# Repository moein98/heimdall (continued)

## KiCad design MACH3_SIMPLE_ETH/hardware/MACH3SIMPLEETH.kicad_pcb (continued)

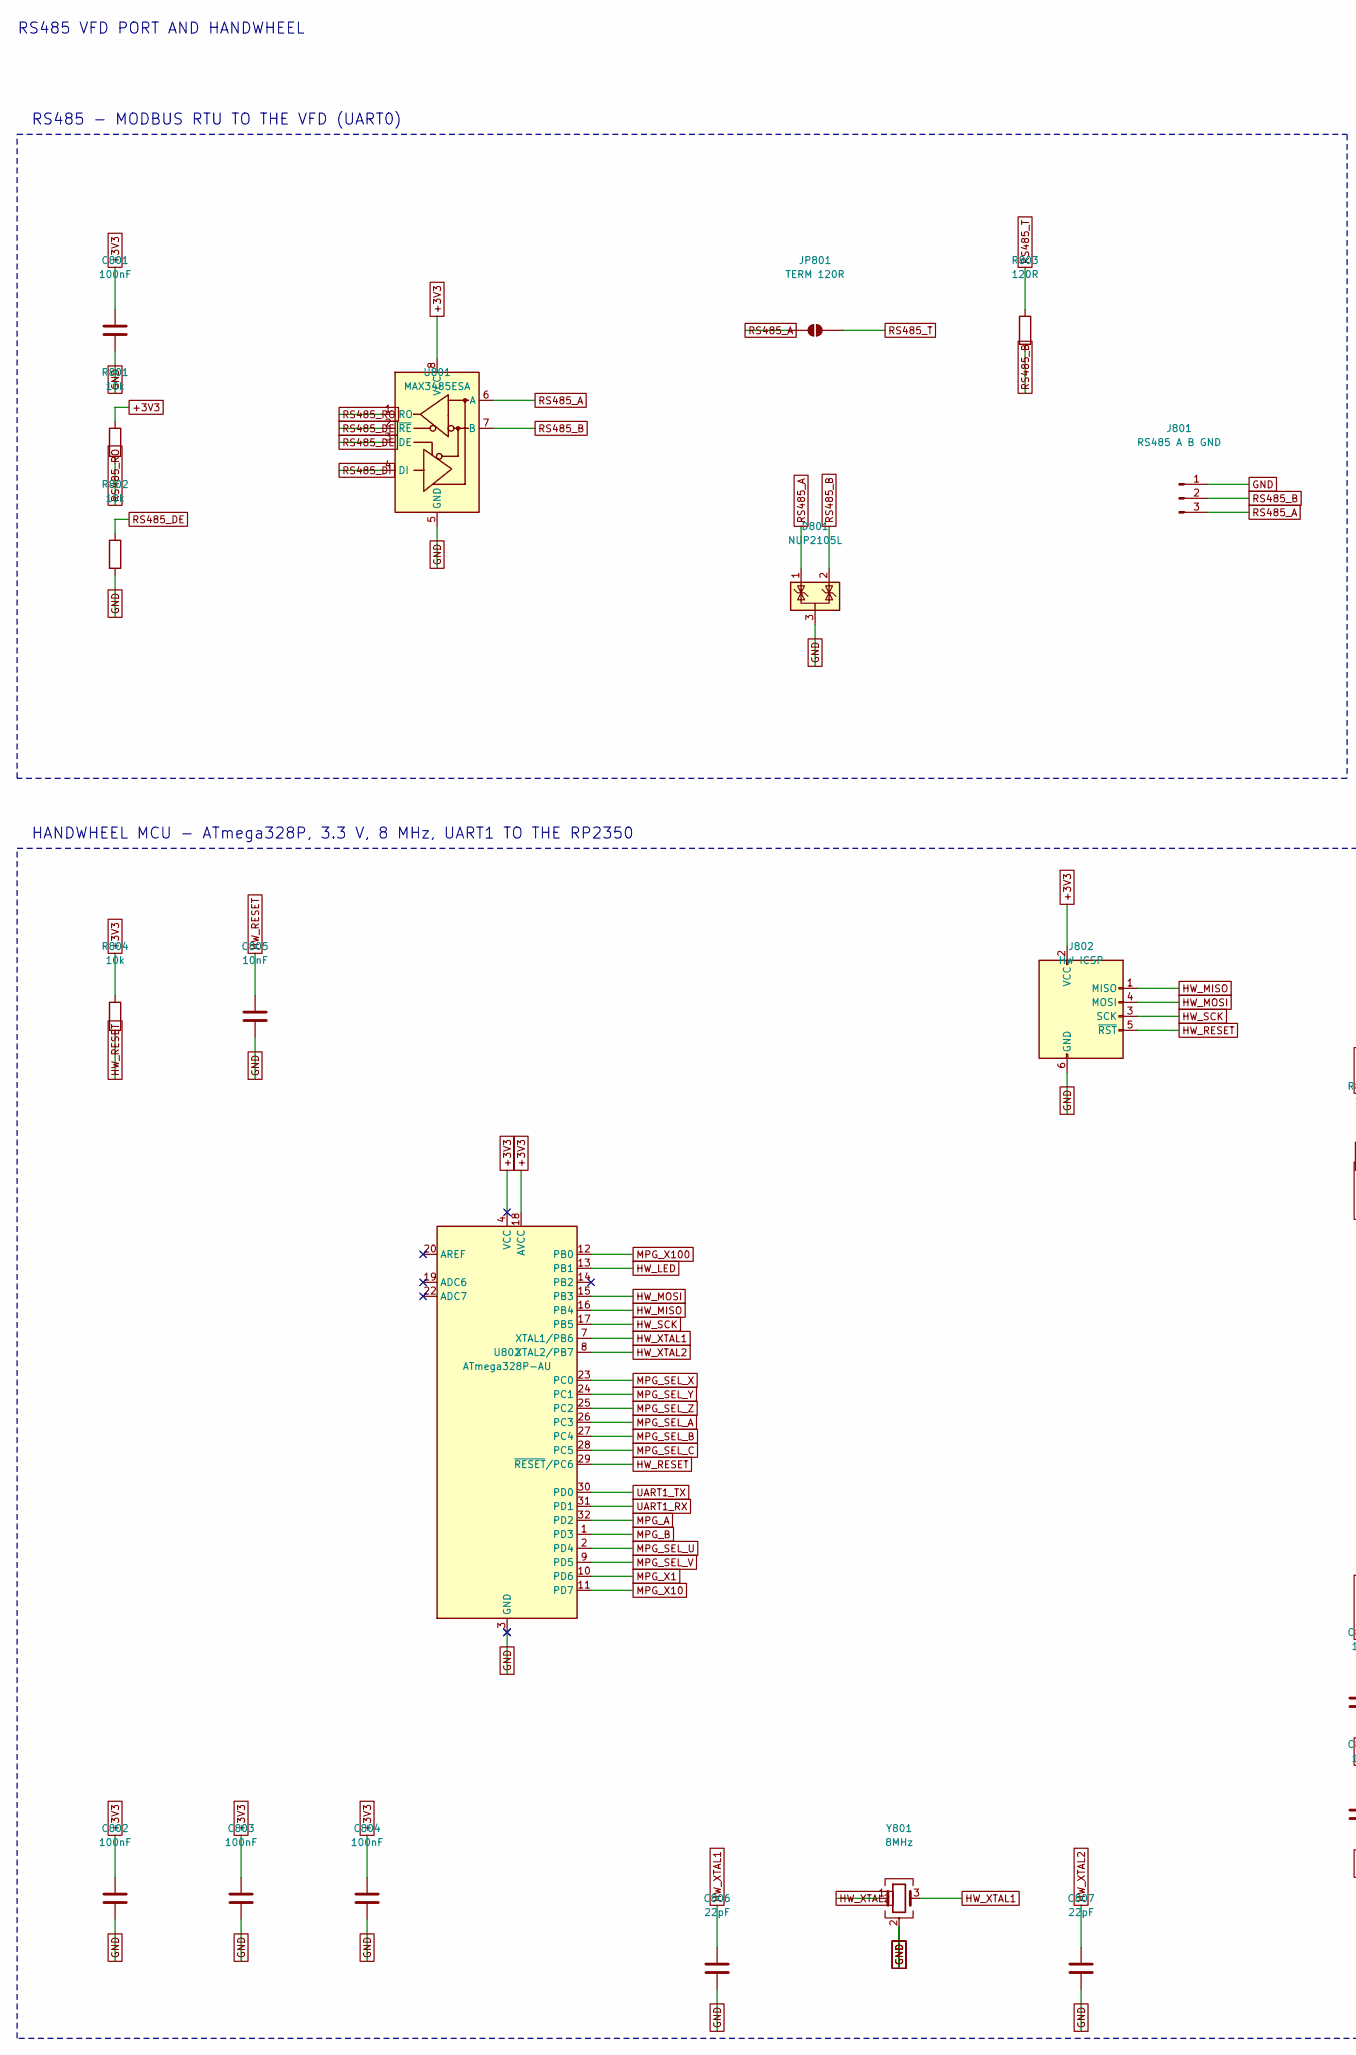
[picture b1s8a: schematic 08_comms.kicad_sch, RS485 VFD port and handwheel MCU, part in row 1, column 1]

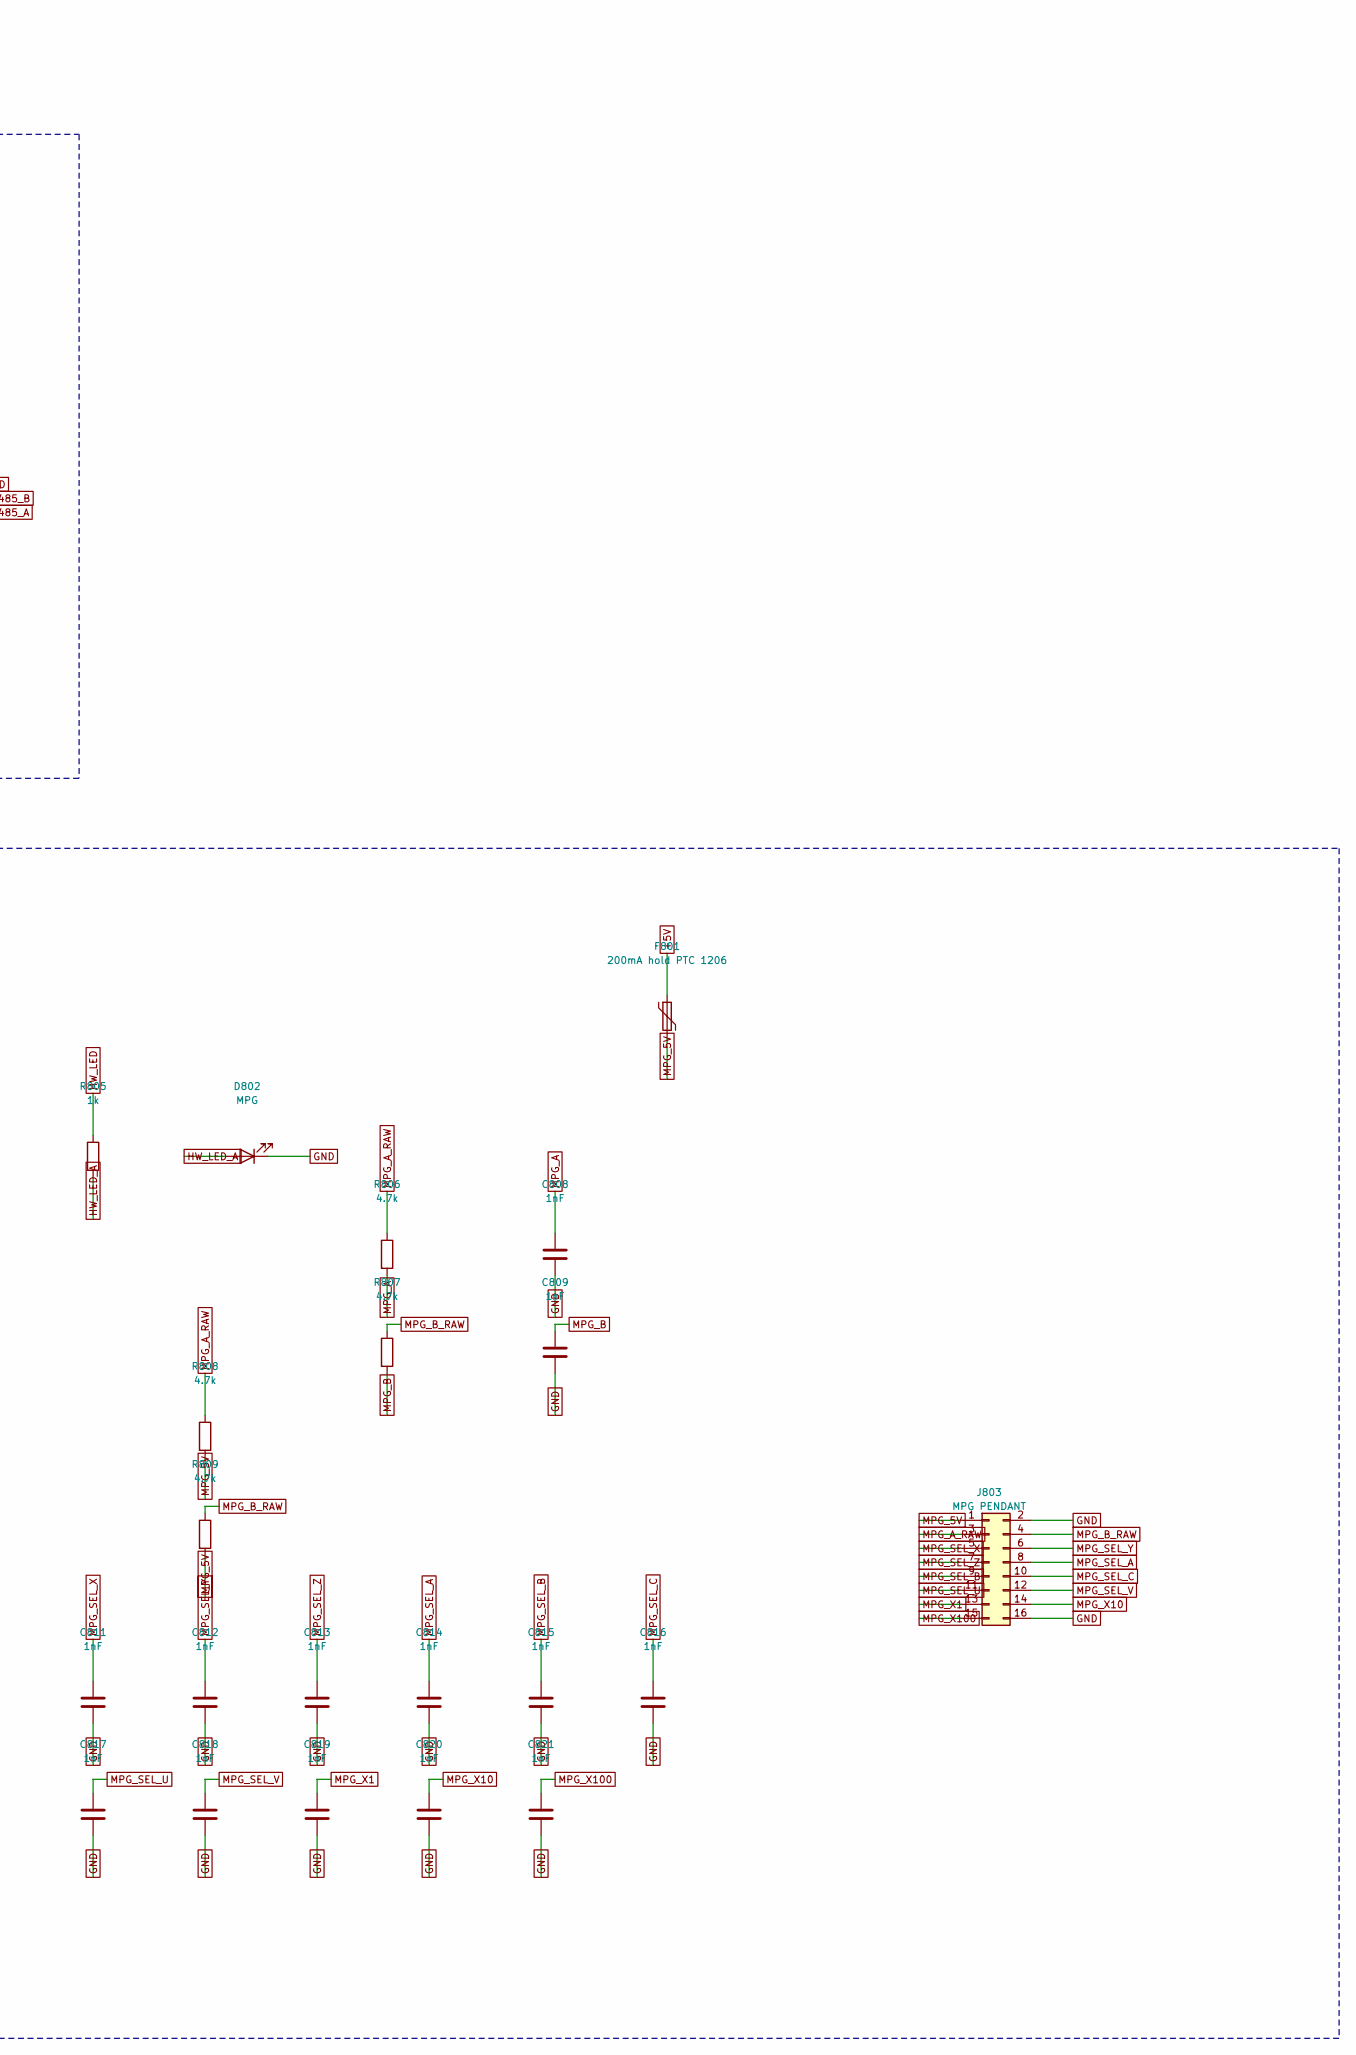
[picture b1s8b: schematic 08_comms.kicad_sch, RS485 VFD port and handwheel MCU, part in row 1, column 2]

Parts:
C801, C802, C803, C804: 100nF; C_0603_1608Metric
C805: 10nF; C_0603_1608Metric
C806, C807: 22pF; C_0603_1608Metric
C808, C809, C811, C812, C813, C814, C815, C816, C817, C818, C819, C820, C821: 1nF; C_0603_1608Metric
D801: NUP2105L; SOT-23
D802: MPG; LED_0603_1608Metric
F801: 200mA hold PTC 1206; Fuse_1206_3216Metric
J801: RS485 A B GND; TerminalBlock_Phoenix_MKDS-1,5-3_1x03_P5.00mm_Horizontal
J802: HW ICSP; PinHeader_2x03_P2.54mm_Vertical
J803: MPG PENDANT; IDC-Header_2x08_P2.54mm_Vertical
JP801: TERM 120R; SolderJumper-2_P1.3mm_Open_RoundedPad1.0x1.5mm
R801, R802, R804: 10k; R_0603_1608Metric
R803: 120R; R_0603_1608Metric
R805: 1k; R_0603_1608Metric
R806, R807, R808, R809: 4.7k; R_0603_1608Metric
U801: MAX3485ESA; SOIC-8_3.9x4.9mm_P1.27mm
U802: ATmega328P-AU; TQFP-32_7x7mm_P0.8mm
Y801: 8MHz; Crystal_SMD_3225-4Pin_3.2x2.5mm

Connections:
+3V3: C801.1, C802.1, C803.1, C804.1, J802.2 (VCC), R801.1, R804.1, U801.8 (VCC), U802.4 (VCC), U802.6 (VCC), U802.18 (AVCC); also elsewhere on the board
+5V: F801.1; also elsewhere on the board
GND: C801.2, C802.2, C803.2, C804.2, C805.2, C806.2, C807.2, C808.2, C809.2, C811.2, C812.2, C813.2, C814.2, C815.2, C816.2, C817.2, C818.2, C819.2, C820.2, C821.2, D801.3 (A), D802.1 (K), J801.1, J802.6 (GND), J803.2, J803.16, R802.2, U801.5 (GND), U802.3 (GND), U802.5 (GND), U802.21 (GND), Y801.2 (G), Y801.4 (G); also elsewhere on the board
HW_LED: R805.1, U802.13 (PB1)
HW_LED_A: D802.2 (A), R805.2
HW_MISO: J802.1 (MISO), U802.16 (PB4)
HW_MOSI: J802.4 (MOSI), U802.15 (PB3)
HW_RESET: C805.1, J802.5 (~RST), R804.2, U802.29 (~RESET/PC6)
HW_SCK: J802.3 (SCK), U802.17 (PB5)
HW_XTAL1: C806.1, U802.7 (XTAL1/PB6), Y801.3
HW_XTAL2: C807.1, U802.8 (XTAL2/PB7), Y801.1
MPG_5V: F801.2, J803.1, R808.2, R809.2
MPG_A: C808.1, R806.2, U802.32 (PD2)
MPG_A_RAW: J803.3, R806.1, R808.1
MPG_B: C809.1, R807.2, U802.1 (PD3)
MPG_B_RAW: J803.4, R807.1, R809.1
MPG_SEL_A: C814.1, J803.8, U802.26 (PC3)
MPG_SEL_B: C815.1, J803.9, U802.27 (PC4)
MPG_SEL_C: C816.1, J803.10, U802.28 (PC5)
MPG_SEL_U: C817.1, J803.11, U802.2 (PD4)
MPG_SEL_V: C818.1, J803.12, U802.9 (PD5)
MPG_SEL_X: C811.1, J803.5, U802.23 (PC0)
MPG_SEL_Y: C812.1, J803.6, U802.24 (PC1)
MPG_SEL_Z: C813.1, J803.7, U802.25 (PC2)
MPG_X1: C819.1, J803.13, U802.10 (PD6)
MPG_X10: C820.1, J803.14, U802.11 (PD7)
MPG_X100: C821.1, J803.15, U802.12 (PB0)
RS485_A: D801.1 (K), J801.3, JP801.1 (A), U801.6 (A)
RS485_B: D801.2 (K), J801.2, R803.2, U801.7 (B)
RS485_DE: R802.1, U801.2 (~RE), U801.3 (DE); also elsewhere on the board
RS485_DI: U801.4 (DI); also elsewhere on the board
RS485_RO: R801.2, U801.1 (RO); also elsewhere on the board
RS485_T: JP801.2 (B), R803.1
UART1_RX: U802.31 (PD1); also elsewhere on the board
UART1_TX: U802.30 (PD0); also elsewhere on the board

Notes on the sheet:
RS485 VFD PORT AND HANDWHEEL
RS485 - MODBUS RTU TO THE VFD (UART0)
HANDWHEEL MCU - ATmega328P, 3.3 V, 8 MHz, UART1 TO THE RP2350

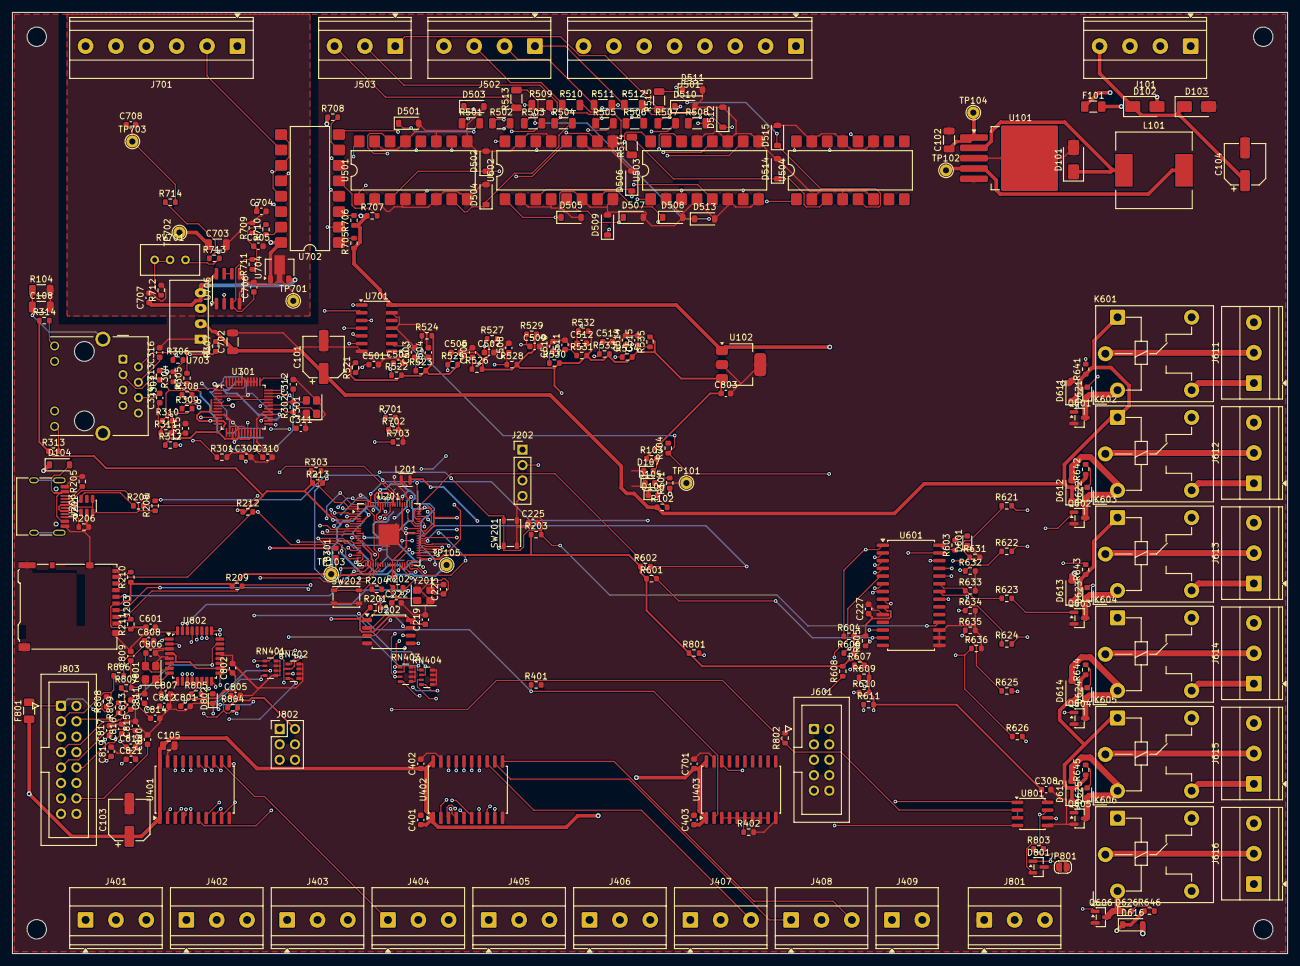
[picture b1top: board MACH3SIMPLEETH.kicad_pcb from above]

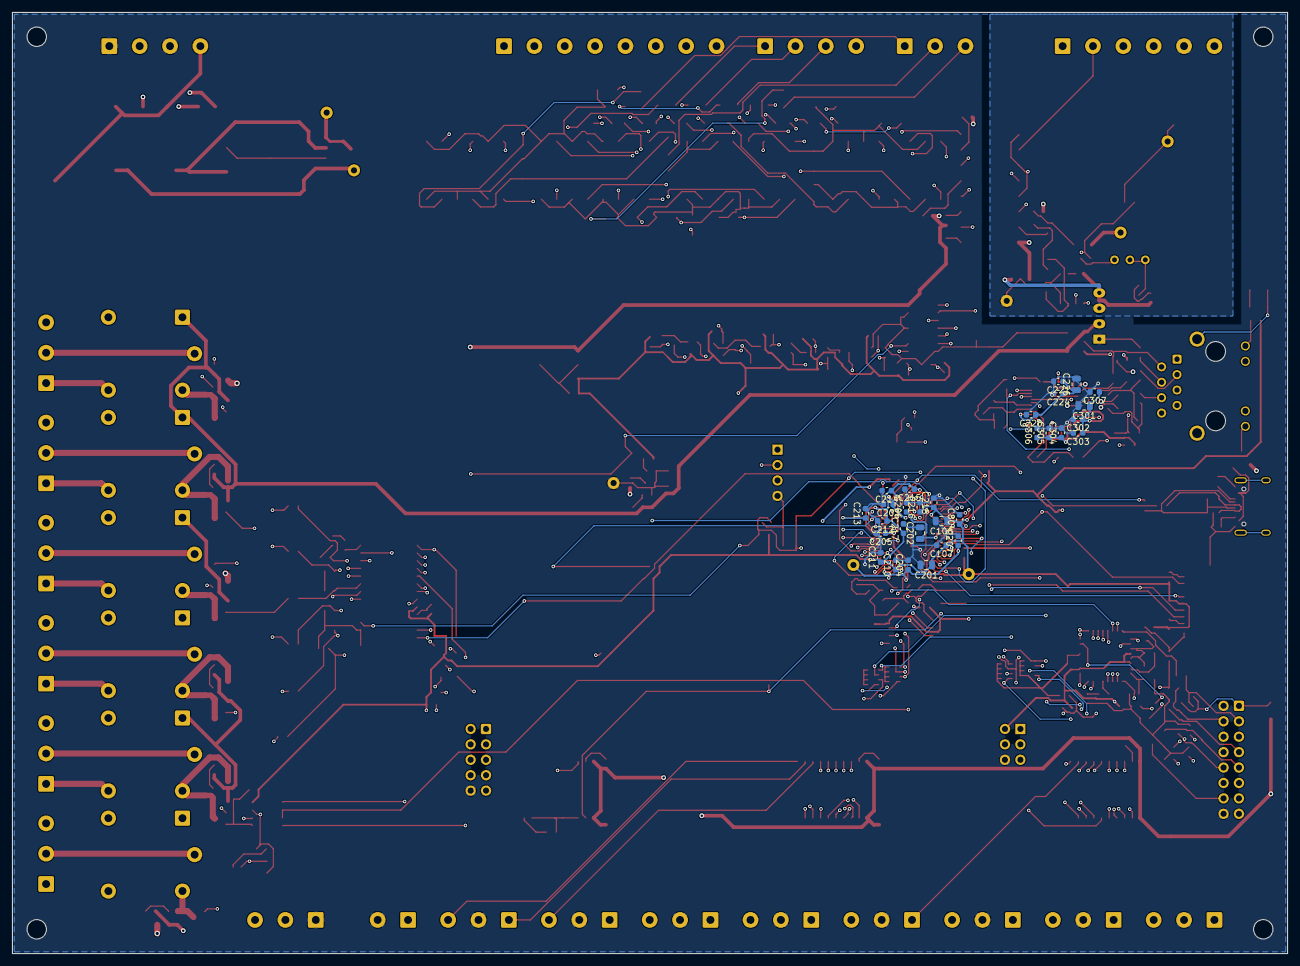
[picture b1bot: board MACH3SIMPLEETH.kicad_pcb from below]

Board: 4 copper layers, 210.0 x 155.0 mm, 337 parts (30 on the bottom side), 257 nets.

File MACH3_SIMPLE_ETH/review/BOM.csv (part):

"Reference","Value","Footprint"
"C101","47uF 50V","Capacitor_SMD:CP_Elec_6.3x7.7"
"C102","1uF 50V X7R","Capacitor_SMD:C_1206_3216Metric"
"C103","220uF 16V low ESR","Capacitor_SMD:CP_Elec_6.3x7.7"
"C104","47uF 50V","Capacitor_SMD:CP_Elec_6.3x7.7"
"C105","10uF 16V X7R","Capacitor_SMD:C_0805_2012Metric"
"C106","10uF 16V X7R","Capacitor_SMD:C_0805_2012Metric"
"C107","100nF","Capacitor_SMD:C_0603_1608Metric"
"C108","1nF 2kV X7R 1206","Capacitor_SMD:C_1206_3216Metric"
"C201","10uF 0805 X5R","Capacitor_SMD:C_0805_2012Metric"
"C202","10uF 0805 X5R","Capacitor_SMD:C_0805_2012Metric"
"C203","2.2uF","Capacitor_SMD:C_0603_1608Metric"
"C204","100nF","Capacitor_SMD:C_0603_1608Metric"
"C205","100nF","Capacitor_SMD:C_0603_1608Metric"
"C206","100nF","Capacitor_SMD:C_0603_1608Metric"
"C207","1uF","Capacitor_SMD:C_0603_1608Metric"
"C210","100nF","Capacitor_SMD:C_0603_1608Metric"
"C211","100nF","Capacitor_SMD:C_0603_1608Metric"
"C212","100nF","Capacitor_SMD:C_0603_1608Metric"
"C213","100nF","Capacitor_SMD:C_0603_1608Metric"
"C214","100nF","Capacitor_SMD:C_0603_1608Metric"
"C215","100nF","Capacitor_SMD:C_0603_1608Metric"
"C216","100nF","Capacitor_SMD:C_0603_1608Metric"
"C217","100nF","Capacitor_SMD:C_0603_1608Metric"
"C218","100nF","Capacitor_SMD:C_0603_1608Metric"
"C219","100nF","Capacitor_SMD:C_0603_1608Metric"
"C220","100nF","Capacitor_SMD:C_0603_1608Metric"
"C221","4.7uF","Capacitor_SMD:C_0603_1608Metric"
"C222","15pF","Capacitor_SMD:C_0603_1608Metric"
"C223","15pF","Capacitor_SMD:C_0603_1608Metric"
"C224","100nF","Capacitor_SMD:C_0603_1608Metric"
"C225","1uF","Capacitor_SMD:C_0603_1608Metric"
"C226","10uF 0805","Capacitor_SMD:C_0805_2012Metric"
"C227","100nF","Capacitor_SMD:C_0603_1608Metric"
"C301","10uF 0805","Capacitor_SMD:C_0805_2012Metric"
"C302","100nF","Capacitor_SMD:C_0603_1608Metric"
"C303","100nF","Capacitor_SMD:C_0603_1608Metric"
"C304","100nF","Capacitor_SMD:C_0603_1608Metric"
"C305","100nF","Capacitor_SMD:C_0603_1608Metric"
"C306","100nF","Capacitor_SMD:C_0603_1608Metric"
"C307","100nF","Capacitor_SMD:C_0603_1608Metric"
"C308","100nF","Capacitor_SMD:C_0603_1608Metric"
"C309","4.7uF","Capacitor_SMD:C_0603_1608Metric"
"C310","100nF","Capacitor_SMD:C_0603_1608Metric"
"C311","18pF","Capacitor_SMD:C_0603_1608Metric"
"C312","18pF","Capacitor_SMD:C_0603_1608Metric"
"C313","6.8nF","Capacitor_SMD:C_0603_1608Metric"
"C314","6.8nF","Capacitor_SMD:C_0603_1608Metric"
"C315","100nF","Capacitor_SMD:C_0603_1608Metric"
"C316","22nF","Capacitor_SMD:C_0603_1608Metric"
"C401","100nF","Capacitor_SMD:C_0603_1608Metric"
"C402","100nF","Capacitor_SMD:C_0603_1608Metric"
"C403","100nF","Capacitor_SMD:C_0603_1608Metric"
"C501","10nF","Capacitor_SMD:C_0603_1608Metric"
"C502","10nF","Capacitor_SMD:C_0603_1608Metric"
"C503","10nF","Capacitor_SMD:C_0603_1608Metric"
"C504","10nF","Capacitor_SMD:C_0603_1608Metric"
"C505","10nF","Capacitor_SMD:C_0603_1608Metric"
"C506","10nF","Capacitor_SMD:C_0603_1608Metric"
"C507","10nF","Capacitor_SMD:C_0603_1608Metric"
"C508","10nF","Capacitor_SMD:C_0603_1608Metric"
"C509","10nF","Capacitor_SMD:C_0603_1608Metric"
"C510","10nF","Capacitor_SMD:C_0603_1608Metric"
"C511","10nF","Capacitor_SMD:C_0603_1608Metric"
"C512","10nF","Capacitor_SMD:C_0603_1608Metric"
"C513","10nF","Capacitor_SMD:C_0603_1608Metric"
"C514","10nF","Capacitor_SMD:C_0603_1608Metric"
"C515","10nF","Capacitor_SMD:C_0603_1608Metric"
"C601","100nF","Capacitor_SMD:C_0603_1608Metric"
"C701","100nF","Capacitor_SMD:C_0603_1608Metric"
"C702","1uF 50V X7R","Capacitor_SMD:C_1206_3216Metric"
"C703","10uF 25V X7R","Capacitor_SMD:C_1206_3216Metric"
"C704","1uF","Capacitor_SMD:C_0603_1608Metric"
"C705","470nF","Capacitor_SMD:C_0603_1608Metric"
"C706","470nF","Capacitor_SMD:C_0603_1608Metric"
"C707","100nF","Capacitor_SMD:C_0603_1608Metric"
"C708","10nF","Capacitor_SMD:C_0603_1608Metric"
"C801","100nF","Capacitor_SMD:C_0603_1608Metric"
"C802","100nF","Capacitor_SMD:C_0603_1608Metric"
"C803","100nF","Capacitor_SMD:C_0603_1608Metric"
"C804","100nF","Capacitor_SMD:C_0603_1608Metric"
"C805","10nF","Capacitor_SMD:C_0603_1608Metric"
"C806","22pF","Capacitor_SMD:C_0603_1608Metric"
"C807","22pF","Capacitor_SMD:C_0603_1608Metric"
"C808","1nF","Capacitor_SMD:C_0603_1608Metric"
"C809","1nF","Capacitor_SMD:C_0603_1608Metric"
"C811","1nF","Capacitor_SMD:C_0603_1608Metric"
"C812","1nF","Capacitor_SMD:C_0603_1608Metric"
"C813","1nF","Capacitor_SMD:C_0603_1608Metric"
"C814","1nF","Capacitor_SMD:C_0603_1608Metric"
"C815","1nF","Capacitor_SMD:C_0603_1608Metric"
"C816","1nF","Capacitor_SMD:C_0603_1608Metric"
"C817","1nF","Capacitor_SMD:C_0603_1608Metric"
"C818","1nF","Capacitor_SMD:C_0603_1608Metric"
"C819","1nF","Capacitor_SMD:C_0603_1608Metric"
"C820","1nF","Capacitor_SMD:C_0603_1608Metric"
"C821","1nF","Capacitor_SMD:C_0603_1608Metric"
"D101","SS34 catch","Diode_SMD:D_SMA"
"D102","SS34 reverse","Diode_SMD:D_SMA"
"D103","SMAJ26A","Diode_SMD:D_SMA"
"D104","B5819W","Diode_SMD:D_SOD-123"
"D105","+5V","LED_SMD:LED_0603_1608Metric"
"D106","V24","LED_SMD:LED_0603_1608Metric"
"D107","+3V3","LED_SMD:LED_0603_1608Metric"
"D501","1N4148W","Diode_SMD:D_SOD-123"
"D502","1N4148W","Diode_SMD:D_SOD-123"
"D503","1N4148W","Diode_SMD:D_SOD-123"
"D504","1N4148W","Diode_SMD:D_SOD-123"
"D505","1N4148W","Diode_SMD:D_SOD-123"
"D506","1N4148W","Diode_SMD:D_SOD-123"
"D507","1N4148W","Diode_SMD:D_SOD-123"
"D508","1N4148W","Diode_SMD:D_SOD-123"
"D509","1N4148W","Diode_SMD:D_SOD-123"
"D510","1N4148W","Diode_SMD:D_SOD-123"
"D511","1N4148W","Diode_SMD:D_SOD-123"
"D512","1N4148W","Diode_SMD:D_SOD-123"
"D513","1N4148W","Diode_SMD:D_SOD-123"
"D514","1N4148W","Diode_SMD:D_SOD-123"
"D515","1N4148W","Diode_SMD:D_SOD-123"
"D601","STATUS","LED_SMD:LED_0603_1608Metric"
"D611","1N4148W flyback","Diode_SMD:D_SOD-123"
"D612","1N4148W flyback","Diode_SMD:D_SOD-123"
"D613","1N4148W flyback","Diode_SMD:D_SOD-123"
"D614","1N4148W flyback","Diode_SMD:D_SOD-123"
"D615","1N4148W flyback","Diode_SMD:D_SOD-123"
"D616","1N4148W flyback","Diode_SMD:D_SOD-123"
"D621","KA","LED_SMD:LED_0603_1608Metric"
"D622","KB","LED_SMD:LED_0603_1608Metric"
"D623","KC","LED_SMD:LED_0603_1608Metric"
"D624","KD","LED_SMD:LED_0603_1608Metric"
"D625","KE","LED_SMD:LED_0603_1608Metric"
"D626","KF","LED_SMD:LED_0603_1608Metric"
"D801","NUP2105L","Package_TO_SOT_SMD:SOT-23"
"D802","MPG","LED_SMD:LED_0603_1608Metric"
"F101","1A slow 1206","Fuse:Fuse_1206_3216Metric"
"F801","200mA hold PTC 1206","Fuse:Fuse_1206_3216Metric"
"FB301","120R@100MHz 0603","Inductor_SMD:L_0603_1608Metric"
"J101","SENSORS / 24V IN","TerminalBlock_Phoenix:TerminalBlock_Phoenix_MKDS-1,5-4_1x04_P5.00mm_Horizontal"
"J201","USB-C","Connector_USB:USB_C_Receptacle_HRO_TYPE-C-31-M-12"
"J202","SWD","Connector_PinHeader_2.54mm:PinHeader_1x04_P2.54mm_Vertical"
"J203","microSD","Connector_Card:microSD_HC_Hirose_DM3AT-SF-PEJM5"
"J301","HR911105A","Connector_RJ:RJ45_Hanrun_HR911105A_Horizontal"
"J401","X axis","TerminalBlock_Phoenix:TerminalBlock_Phoenix_MKDS-1,5-3_1x03_P5.00mm_Horizontal"
"J402","Y axis","TerminalBlock_Phoenix:TerminalBlock_Phoenix_MKDS-1,5-3_1x03_P5.00mm_Horizontal"
"J403","Z axis","TerminalBlock_Phoenix:TerminalBlock_Phoenix_MKDS-1,5-3_1x03_P5.00mm_Horizontal"
"J404","A axis","TerminalBlock_Phoenix:TerminalBlock_Phoenix_MKDS-1,5-3_1x03_P5.00mm_Horizontal"
"J405","B axis","TerminalBlock_Phoenix:TerminalBlock_Phoenix_MKDS-1,5-3_1x03_P5.00mm_Horizontal"
"J406","C axis","TerminalBlock_Phoenix:TerminalBlock_Phoenix_MKDS-1,5-3_1x03_P5.00mm_Horizontal"
"J407","U axis","TerminalBlock_Phoenix:TerminalBlock_Phoenix_MKDS-1,5-3_1x03_P5.00mm_Horizontal"
"J408","V axis","TerminalBlock_Phoenix:TerminalBlock_Phoenix_MKDS-1,5-3_1x03_P5.00mm_Horizontal"
"J409","ENABLE","TerminalBlock_Phoenix:TerminalBlock_Phoenix_MKDS-1,5-2_1x02_P5.00mm_Horizontal"
"J501","LIMITS X Y Z A B C U V","TerminalBlock_Phoenix:TerminalBlock_Phoenix_MKDS-1,5-8_1x08_P5.00mm_Horizontal"
"J502","EST HLD RUN PRB","TerminalBlock_Phoenix:TerminalBlock_Phoenix_MKDS-1,5-4_1x04_P5.00mm_Horizontal"
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
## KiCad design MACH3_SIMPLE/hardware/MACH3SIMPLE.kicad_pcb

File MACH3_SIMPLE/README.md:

# MACH3-SIMPLE (revision A1)

A Mach3 parallel-port breakout board: six buffered step/dir axes, six 24 V
sensor inputs, a handwheel switched between jog and THC, six relays driven
over RS232 by an ATmega328P, and an isolated 0-10 V spindle-speed output with
FWD / REV for a VFD. It reproduces a board already in service and matches its
connector positions. It takes one supply, 24 V; the 5 V rail is made on the
board. Apart from the VFD port there is no galvanic isolation.

| Folder | What is in it |
|---|---|
| `fab/` | **What goes to the board house.** `MACH3SIMPLE-gerbers.zip` (2 layers, 1.6 mm FR4, 1 oz, 150.5 x 137.9 mm), BOM, pick-and-place, PDFs |
| `hardware/` | The KiCad 10 project: `MACH3SIMPLE.kicad_pro` |
| `firmware/` | AVR C source; `build/mach3simple.hex` is the built firmware |
| `docs/` | `SPEC.md` - what the board is and why; `COMMISSIONING.md` - bring-up and test, step by step (Persian) |
| `tools/` | The scripts that generate, check and route the design |
| `review/` | ERC/DRC reports, netlist, schematic PDF, board renders |

## What changed from A0

| | A0 | A1 |
|---|---|---|
| Supplies | 5 V and 24 V, each on its own terminal | **24 V only.** An LM2596S-5.0 buck (`U4`) makes +5V, in the top-right corner beside the 24 V input |
| Relay drivers | 2N7002 drain and source swapped - every relay **stuck on** | Fixed. `check_design.py` now checks every MOSFET's source is on ground |
| Top-edge terminal legends | Printed in reverse: `+24` over 0V, `+5` over the handwheel's B, `EMG` over X home | Fixed: the signals follow the legends, which follow the board in service |
| Input optocouplers | PC847 on a SOIC-16 footprint, which no PC847 fits | SMD DIP-16 (2.54 mm), the package PC847 comes in |
| Opto LED protection | Promised in the notes, missing from the circuit | A reverse diode across every input LED (`D20`-`D25`) |
| Spindle | - | **New:** isolated 0-10 V (`AVI`/`ACM`) and FWD/REV/AUX (`FWD`/`REV`/`AUX`/`DCM`) on `J5`, from port 2 pins 7, 8, 9, 6 |

A1 then had a design review of its own, which added:

| | |
|---|---|
| Relay terminals | legends printed on the back (`RELAY A`, `NO COM NC` under each screw) and `RELAY A`-`F` on the front; A0/A1 had them on F.Fab only, which is not printed |
| Relay LED resistors | 10k instead of 4k7 - 4k7 on 24 V was 103 mW in a 100 mW 0603 |
| Axis buffers | 74AC245 (same pads): 24 mA per output for opto-input drivers |
| Sensor supply | `J4` is four screws: `+24 0V` for the sensors (fused) and `+24 0V` in |
| C2 | 47 uF 50 V - a 100 uF 50 V part does not come in a 6.3 x 7.7 can |
| Labels | `5V`, `24V`, `SERIAL`, relay letters, `10V ADJ` instead of bare designators; a dashed line round the isolated VFD side |
| Test points | `GND` `5V` `24V`, and on the VFD side `ACM` `12V` `AVI` |
| Buck switch node | drawn by hand on the top layer, 14 mm and no vias (was 17 mm with two) |
| Handwheel +5 V | through a 200 mA resettable fuse (`F3`) |
| MCU reset | 10 nF against relay noise |
| VFD `AUX` | the spare optocoupler channel as a fourth VFD contact, port 2 pin 6 |

## Regenerating

The schematic and board are generated by scripts, not drawn by hand. To change
the design, edit `tools/build_project.py` or `tools/build_pcb.py` and
regenerate; an edit made in KiCad is lost at the next regeneration.

    python tools/build_project.py                  # schematic
    D:/KiCad/bin/python.exe tools/build_pcb.py --force   # placement (discards routing)
    D:/KiCad/bin/python.exe tools/autoroute.py export    # then Freerouting, then:
    D:/KiCad/bin/python.exe tools/autoroute.py import
    D:/KiCad/bin/python.exe tools/autoroute.py vfd-export  # then Freerouting on the _vfd DSN
    D:/KiCad/bin/python.exe tools/autoroute.py vfd-import
    D:/KiCad/bin/python.exe tools/autoroute.py stitch
    KICAD_CLI=D:/KiCad/bin/kicad-cli.exe sh tools/validate.sh
    KICAD_CLI=D:/KiCad/bin/kicad-cli.exe sh tools/fab.sh

`build_pcb.py` needs the netlist that `validate.sh` exports (`review/net.net`),
so after a schematic change run `validate.sh` once before placing. It prints
which signal lands under each word of every top-edge legend - read those lines.

## Firmware

`sh firmware/build.sh` runs the tests and builds the hex;
`sh firmware/build.sh flash` also sets the fuses and programs the chip through
the ICSP header `J60` with a USBasp. Serial is 9600 8N1. Commands, sent with
Mach3's `SendSerial`: `A`-`F` relay on, `a`-`f` off, `T` handwheel to THC,
`t` handwheel to jog, `?` status. A1 needs no firmware change.

## Spindle, in Mach3

Port 2 pin 7 is the spindle PWM pin (PWMBase Freq 100 Hz), pin 8 is Output #1
(M3, FWD) and pin 9 Output #2 (M4, REV), all active high. Trim `RV1` for
10.0 V at full PWM. Pin 6 can be Output #3, for `AUX`. `docs/COMMISSIONING.md`,
steps 6 to 8, has the settings.

`mach3 rs232 inputs 6 outputs 6 - pulse 5v - pnp sens.pdf` is the assembly
drawing of the board in service that the layout was copied from.

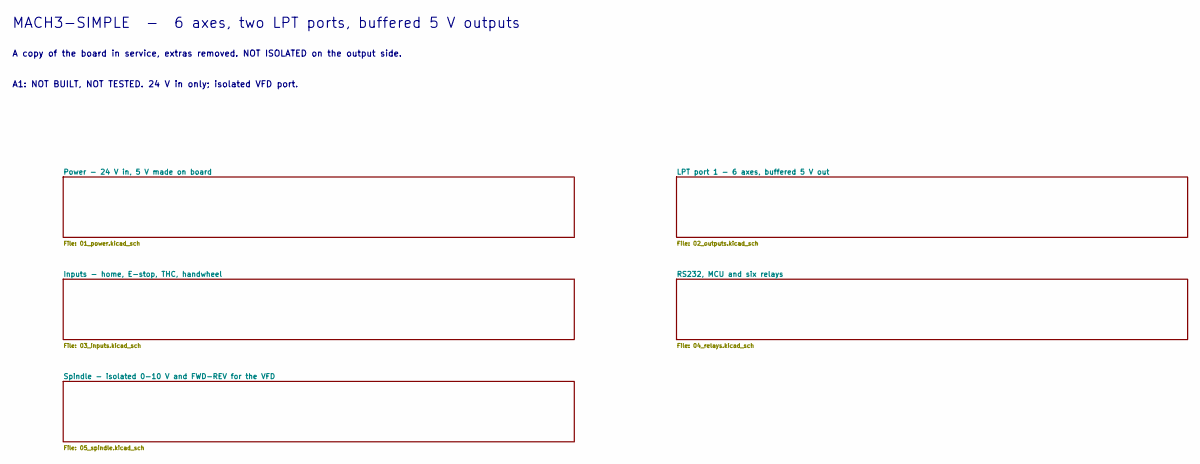
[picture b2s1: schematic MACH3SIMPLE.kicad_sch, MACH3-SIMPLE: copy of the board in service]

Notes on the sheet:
MACH3-SIMPLE - 6 axes, two LPT ports, buffered 5 V outputs
A copy of the board in service, extras removed. NOT ISOLATED on the output side.
A1: NOT BUILT, NOT TESTED. 24 V in only; isolated VFD port.

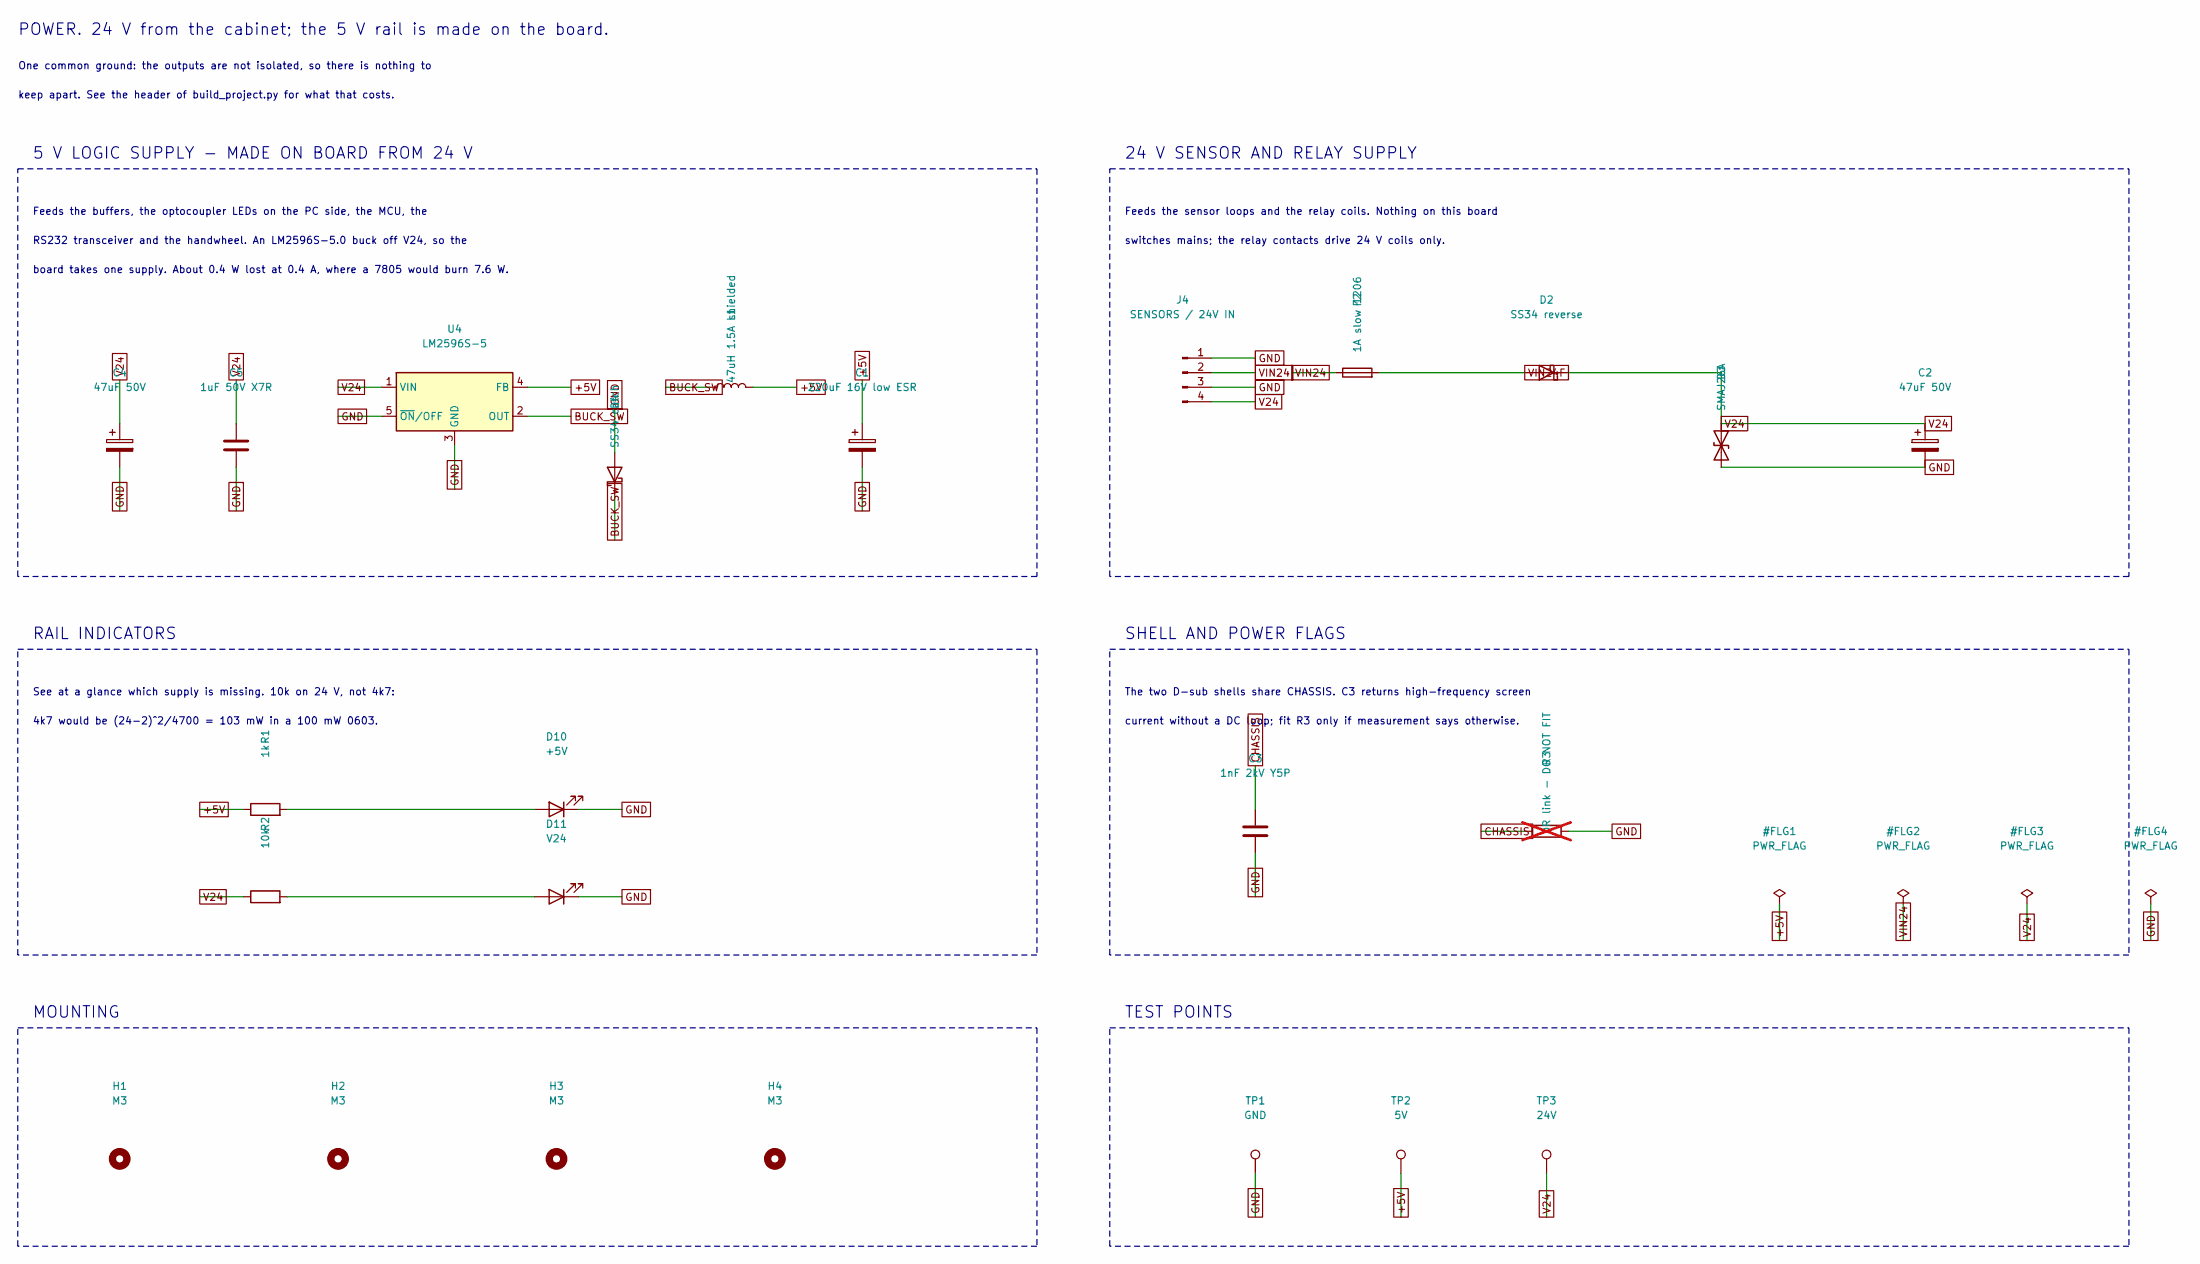
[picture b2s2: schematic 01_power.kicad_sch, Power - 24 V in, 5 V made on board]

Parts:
C1: 220uF 16V low ESR; CP_Elec_6.3x7.7
C2, C4: 47uF 50V; CP_Elec_6.3x7.7
C3: 1nF 2kV Y5P; C_Disc_D5.0mm_W2.5mm_P5.00mm
C5: 1uF 50V X7R; C_1206_3216Metric
D2: SS34 reverse; D_SMA
D3: SMAJ26A; D_SMA
D4: SS34 catch; D_SMA
D10: +5V; LED_0603_1608Metric
D11: V24; LED_0603_1608Metric
F2: 1A slow 1206; Fuse_1206_3216Metric
H1, H2, H3, H4: M3; MountingHole_3.2mm_M3
J4: SENSORS / 24V IN; TerminalBlock_Phoenix_MKDS-1,5-4_1x04_P5.00mm_Horizontal
L1: 47uH 1.5A shielded; L_12x12mm_H8mm
R1: 1k; R_0603_1608Metric
R2: 10k; R_0603_1608Metric
R3: 0R link - DO NOT FIT; R_1206_3216Metric; not fitted
TP1: GND; TestPoint_THTPad_D2.0mm_Drill1.0mm
TP2: 5V; TestPoint_THTPad_D2.0mm_Drill1.0mm
TP3: 24V; TestPoint_THTPad_D2.0mm_Drill1.0mm
U4: LM2596S-5; TO-263-5_TabPin3

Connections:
+5V: C1.1, L1.2, R1.1, TP2.1, U4.4 (FB); also elsewhere on the board
BUCK_SW: D4.1 (K), L1.1, U4.2 (OUT)
CHASSIS: C3.1, R3.1; also elsewhere on the board
GND: C1.2, C2.2, C3.2, C4.2, C5.2, D3.2 (A2), D4.2 (A), D10.1 (K), D11.1 (K), J4.1, J4.3, R3.2, TP1.1, U4.3 (GND), U4.5 (~ON/OFF); also elsewhere on the board
unnamed: D10.2 (A), R1.2
unnamed: D11.2 (A), R2.2
V24: C2.1, C4.1, C5.1, D2.1 (K), D3.1 (A1), J4.4, R2.1, TP3.1, U4.1 (VIN); also elsewhere on the board
VIN24: F2.1, J4.2
VIN24F: D2.2 (A), F2.2

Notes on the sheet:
POWER. 24 V from the cabinet; the 5 V rail is made on the board.
One common ground: the outputs are not isolated, so there is nothing to
keep apart. See the header of build_project.py for what that costs.
5 V LOGIC SUPPLY - MADE ON BOARD FROM 24 V
Feeds the buffers, the optocoupler LEDs on the PC side, the MCU, the
RS232 transceiver and the handwheel. An LM2596S-5.0 buck off V24, so the
board takes one supply. About 0.4 W lost at 0.4 A, where a 7805 would burn 7.6 W.
24 V SENSOR AND RELAY SUPPLY
Feeds the sensor loops and the relay coils. Nothing on this board
switches mains; the relay contacts drive 24 V coils only.
RAIL INDICATORS
See at a glance which supply is missing. 10k on 24 V, not 4k7:
4k7 would be (24-2)^2/4700 = 103 mW in a 100 mW 0603.
SHELL AND POWER FLAGS
The two D-sub shells share CHASSIS. C3 returns high-frequency screen
current without a DC loop; fit R3 only if measurement says otherwise.
TEST POINTS
MOUNTING
